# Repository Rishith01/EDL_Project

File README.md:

<!-- Do Not Change the below line. It will affect your workflow badge -->

<!-- ADD YOUR CHANGES AFTER THIS LINE -->

# SACE(Secure Adaptive Continuum Explorer)
**Team TUE-16 | Indian Institute of Technology Bombay**

---

## Team Members
* **Arijit Paul** (23B1219)
* **Arshit Singh** (23B1275)
* **Prithvi Sangam** (23B1292)
* **Rishith Gupta** (23B1234)
* **Veeresh S K** (23B1309)

---

## Project Abstract
This project investigates the practical implementation of **soft robotics** through the development of a modular, tentacle-based end effector on a continuum backbone. The system is engineered to navigate highly constrained environments and perform adaptive grasping of irregular objects. 

The architecture consists of a **continuum robotic arm featuring four flexible segments** capable of extending from a compact enclosure. By integrating 10 degrees of freedom (DOF), tendon-driven actuation, and real-time visual feedback, the robot demonstrates the capability of compliant structures to achieve dexterity and safety in applications where traditional rigid-link manipulators are insufficient.

---

## Key Technical Features
* **Deployable Mechanism:** Engineered for high spatial efficiency, allowing the arm to extend from a compact housing for maximum reach-to-storage ratio.
* **Continuum Kinematics:** A multi-link flexible structure that facilitates smooth, non-discrete bending for complex maneuvering in tight spaces.
* **Adaptive Morphology:** The tentacle-inspired design conforms naturally to the geometry of target objects, ensuring secure grasping through compliant contact.
* **Teleoperated Control:** Real-time operation via a gaming controller/click based interface, mapping user input directly to multi-segment motion.
* **Integrated Vision System:** An endoscope camera provides a live stream to the operator for precise navigation and targeting.
* **Active Safety Array:** Integrated limit switches detect external obstacles and mechanical limits to prevent system damage and ensure safe motion.
* **Modularity:** The system is partitioned into independent subsystems, allowing for streamlined repair, scaling, and iterative refinement.

---

## System Overview

### Hardware Architecture
* **Controller Architecture:** Dual Raspberry Pi Pico microcontrollers configured in a Master–Slave hierarchy to distribute real-time processing loads.
* **Motor Control:** Three Adafruit FeatherWing Motor Drivers, selected for their high-density power management and compact footprint.
* **Actuation:** 11 N20 micro-gear motors dedicated to tendon-driven link manipulation through specialized differential spools.
* **Sensing Array:** 16 Limit Switches (distributed as 4 per continuum segment) for obstacle detection and motion constraint.
* **Vision:** A high-resolution endoscope camera module for front-facing orientation and feedback with 60 degree field of view.
* **Electronics:** A custom-designed PCB for efficient power distribution and signal routing, including 12V to 3.3V power conversion.

### Software Architecture
* **Workstation Logic:** Python-based control scripts on the laptop for signal processing, controller mapping, and user interface management.
* **Embedded Firmware:** MicroPython-based scripts running on the Raspberry Pi Pico for low-level hardware control and motor actuation.
* **Visual Pipeline:** Python-based live feed processing for real-time operator guidance.
The flowcharts and execution logic are present in the folder READMEs. Refer to particular folder for more details.
---

## Working Principle
1.  **Input Acquisition:** The operator provides motion commands through a gaming controller/click and keyboard interface.
2.  **Signal Processing:** The laptop-based Python environment translates given commands into specific link-actuation commands and calculates which link is to move how much using our control algorithm.
3.  **Command Dispatch:** Control signals are transmitted to the Master Raspberry Pi Pico.
4.  **Distributed Execution:** The Master Pico coordinates with the Slave Pico and the motor driver array to execute precise motor rotations.
5.  **Actuation:** N20 motors rotate the differential spools, pulling tendons to induce controlled bending in the continuum segments.
6.  **Feedback Loop:** Real-time visual data from the camera and tactile data from the limit switches are monitored to guide navigation and prevent collisions.

---

## Final Deliverables

The project delivers a fully functional soft robotic system with the following capabilities:

- **Continuum Robotic Arm System**
  - A four-segment tendon-driven continuum arm capable of smooth, multi-directional bending  
  - Designed to navigate constrained environments with high flexibility  

- **Tentacle-Based End Effector**
  - A compliant gripper capable of adaptive grasping of irregular objects  
  - Independently actuated for controlled gripping  

- **Teleoperation Interface**
  - Real-time control using keyboard, mouse, and gaming controller  
  - Supports intuitive interaction through a camera-based interface  

- **Vision-Guided Operation**
  - Integrated endoscope camera providing live visual feedback  
  - Enables precise navigation and targeting  

- **Safety Mechanism**
  - Limit switch array for obstacle detection and motion constraint  
  - Automatic escape responses to prevent system damage  

- **Custom Embedded Control System**
  - Dual Raspberry Pi Pico architecture (Master–Slave)  
  - Distributed control for motor actuation and hardware interfacing  

- **Mechanical and Electronic Integration**
  - Fully assembled system including:
    - Custom PCB  
    - Motor driver integration  
    - Tendon-driven actuation system  

- **User Interface and Control Software**
  - Python-based host system for trajectory planning and control  
  - MicroPython firmware for real-time embedded execution  

---

## Repository Structure

```plaintext
├── src/                # Source code (MicroPython + Python)
├── pcb/                # PCB designs and schematics
│   └── PCB1/
│       ├── design.brd
│       ├── schematic.src
│       └── pictures/   # Fabricated PCB and Fusion 360 layouts
├── 3d_models/          # CAD models (Fusion 360)
│   ├── tentacle/
│   ├── continuum/
│   ├── base_plate/
|   ├── enclosure/
│   ├── spool/
|   └── motor_mount/
├── reports/            # Project Milestone Documentation
│   ├── milestone0/
│   ├── milestone1/
│   ├── milestone2/
|   ├── milestone3/
│   └── milestone4/
├── others/
│   ├── user_manual/    # Operational instructions
│   ├── presentation/   # System demonstration
|       ├── slides/
│       └── video/    
|   ├── images/         # Images of final setup
|   ├── extras/         # Extra images and videos
|   └── diagrams/       # Relevant diagrams
├── bom.xls             # Detailed Bill of Materials
└── README.md
```

## Repository Walkthrough

### src/
Contains all source code for the system, including:
- MicroPython code for the Raspberry Pi Pico, master and slave RPi (motor control, hardware interfacing)
- Python-based host code for user interaction, trajectory planning, and communication  

Each subfolder is organized based on the execution platform and includes relevant README files describing usage and setup.

---

### pcb/
Includes all PCB-related design files and documentation:
- Schematic and layout files for the custom PCB  
- Fabrication outputs and board design files  
- Images of the fabricated PCB and assembled boards  

The PCB integrates motor drivers, power distribution, and control interfaces required for system operation.

---

### 3d_models/
Contains all mechanical CAD designs used in the project.  
The models are organized into subsystem-level folders:
- **tentacle and top_link/** – End-effector for gripping and top link continuum link
- **continuum/** – Flexible links enabling motion  
- **base_plate/** – Structural base and motor mounting  
- **enclosure/** – Outer housing (laser-cut design)  
- **spools/** – Tendon winding mechanisms  
- **Motor Mount/** – Motor holding structures  

Each folder includes design files, images, and descriptions of functionality and assembly.

---

### reports/
Contains all milestone reports documenting the project lifecycle:
- Concept development  
- Design iterations  
- Implementation progress  
- Final system evaluation  

All reports are provided in PDF format.

---

### others/
Contains supporting materials required for understanding and operating the system:
- **user_manual/** – Step-by-step instructions for setup and operation  
- **presentation/** – Slides and demonstration video  
- **images/** – Photographs of the final assembled system  
- **diagrams/** – Wiring diagrams and system-level representations
- **extras/** - Extra images and videos during testing and prototyping

---

### bom.xls
A detailed Bill of Materials listing all components used in the project, including:
- Electronic components  
- Mechanical parts  
- Consumables and fabrication materials  

Each entry includes quantity, description, and source information.

---

### README.md
The root documentation file providing:
- Project overview and objectives  
- System description  
- Repository structure  
- Key features and functionality  
---

## Technical Constraints and Operational Limits
The current design represents a balance between mechanical performance and the physical limitations of the materials and space.

1. **Bending Threshold**: Empirical testing established a stable operational limit of approximately 30° per link. Beyond this angle, mechanical stress increases significantly, contributing to tendon slack issues within the actuation system.

2. **Control Paradigm**: Currently restricted to manual teleoperation; autonomous path planning and inverse kinematics are not yet implemented.

3. **Backbone Hysteresis and Droop**: The use of glue gun sticks as a central backbone introduces stability issues. After bending, the backbone may fail to return to a perfectly linear state, causing the robot to droop. Ensuring the backbone is fixed at the start and end of each link segment is critical for maintaining a consistent neutral axis.

4. **Tendon Dynamics**: Issues regarding tendon slack and potential thread interference in the shared spool design persist during extreme ranges of motion.

---

## Course Reflection and Learnings

### Technical Learnings

This project provided hands-on experience across multiple domains:

- **Mechanical Design**
  - Designing for tolerances and iterative prototyping  
  - Understanding trade-offs between flexibility and structural strength  
  - Challenges in tendon-driven systems such as slack and routing  

- **Embedded Systems**
  - Working with dual microcontroller architecture (Master–Slave)  
  - Interfacing peripherals such as motor drivers, encoders, and port expanders  
  - Handling real-time constraints in MicroPython  

- **Control Systems**
  - Implementing coordinated multi-link motion  
  - Understanding limitations of open-loop control  
  - Practical challenges in achieving smooth motion  

- **PCB Design**
  - Designing and debugging custom PCBs  
  - Managing power distribution and signal routing  
  - Handling hardware failures and component sensitivity  

- **System Integration**
  - Combining mechanical, electrical, and software subsystems  
  - Debugging issues arising only during full system integration  

---

### Team Challenges and Adaptation

- **Subsystem Isolation and Testing**
  - Each subsystem (mechanical, electronics, software) was tested independently before integration  
  - This helped in identifying issues early and reducing debugging complexity  

- **Iterative Prototyping**
  - Multiple iterations were required, especially for:
    - Spool design  
    - Tentacle structure  
    - Continuum links  
  - Rapid prototyping enabled quick validation and refinement  

- **Cross-Domain Collaboration**
  - Team members developed working knowledge of other subsystems  
  - Ensured continuity when specific members were unavailable  

- **Integration Challenges**
  - Most issues arose during integration rather than individual subsystem development  
  - Required coordinated debugging sessions and time alignment among team members  

---

### Honest Reflection

- While the final system achieves the intended functionality, a significant portion of the effort was spent resolving **practical engineering challenges** rather than implementing advanced features  

- Mechanical reliability (tolerances, tendon routing, slack management) proved to be more critical and time-consuming than initially anticipated  

- Hardware failures (motor drivers, microcontrollers) highlighted the importance of robust electrical design and protection  

- The control system works effectively for manual operation, but lacks higher-level intelligence and automation  

- Overall, the project demonstrates a **working proof-of-concept**, but not a fully optimized or production-ready system  

---

### Incomplete Features and Limitations

The following aspects remain incomplete:

- **Autonomous Control**
  - No implementation of inverse kinematics or automated path planning  
  - Reason: Complexity of modeling continuum kinematics and time constraints  

- **Closed-Loop Feedback**
  - Limited use of encoder data for precise control  
  - Reason: Integration complexity and prioritization of basic functionality  

- **Robust Tendon Management**
  - Issues with slack, overlap, and spool behavior at extreme motions  
  - Reason: Mechanical design constraints and limited iteration time  

- **System Stability**
  - Vibrations and minor inaccuracies in motion  
  - Reason: Structural limitations and compact design constraints  

---

### Future Work 

- **Inverse Kinematics for Continuum Arms**
  - Develop simplified models for controlled positioning  

- **Improved Tendon Mechanism**
  - Dedicated spool designs with better separation and tension control  

- **Enhanced Feedback Control**
  - Utilize encoder data for closed-loop control  
  - Implement PID-based corrections  

- **Structural Improvements**
  - Replace glue stick backbone with engineered compliant structures  

- **Miniaturization**
  - Redesign base plate and enclosure for reduced footprint  

- **System Robustness**
  - Add electrical protection (snubbers, proper grounding, shielding)  

---

## Acknowledgements
We extend our sincere gratitude to Prof. Siddharth Tallur, Prof. Himanshu Bahirat, and Prof. P. C. Pandey for their continuous guidance and valuable insights throughout this project. We also acknowledge the support of Ankur, Maheshwar, the WEL RAs and TAs for their technical assistance during the development and debugging phases.

## Inspiration 
The inspiration for the tentacle end effector came from this youtube video of the spirobs bot: https://m.youtube.com/watch?v=Q2yYclPaEV0

Inspiration for the continuum arm came from this video from continnum robotics lab of university of toronto. https://m.youtube.com/watch?v=MxBeUQay8YM

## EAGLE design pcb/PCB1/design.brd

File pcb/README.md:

# PCB information and Post-Fabrication Modifications

This PCB was designed using **Autodesk Fusion 360 (Fusion Electronics)**. It consists of 2 RPIs(both communicate over I2C, one is connected to the laptop[master] and the other is the slave). Slave RPI collects encoder information and relays it to the main RPI. We did this because we were worried about the computing capability of a single RPI. The master RPI also controls 2 GPIO port expanders[MCP23S17](over SPI), which provide a means to get feedback using the limit switches. This RPI also controls the Adafruit Featherwing motor drivers(via I2C), 3 of the drivers are stacked on top of each other using stackable header pins. It also contains an AMS1117 3.3V LDO to power the logic using a 12V input. More information about the schematic is available in the image below.

Following fabrication, a few manual trace modifications (often referred to as "micro-surgeries" or bodge wires) are required on the physical board to correct an inconsistency with the SPI bus routing.

## Layout issue
### SPI issue
In the initial PCB design, the pin assignments for the **MCP23S17** (specifically the one closest to the Raspberry Pi) were mistakenly split across two different SPI buses. The original, incorrect routing was as follows:

* **`GP6`** (Pin 9, SPI0 SCK) -> MCP23S17 SPI SCK
* **`GP7`** (Pin 10, SPI0 TX) -> MCP23S17 SPI TX
* **`GP8`** (Pin 11, SPI1 RX) -> MCP23S17 SPI RX
* **`GP9`** (Pin 12, SPI0 CS) -> MCP23S17 SPI CS

### RPI VBUS issue
Main RPI's VSYS pin(Pin 39) was connected to the 3.3V power rail on the PCB. The issue was that the main RPI had to be connected to the laptop via a USB cable while operating the robot which caused the VSYS pin to output 5V as it was connected to the power line of the USB. This forced the bus to go to 5V and fried our LDO(AMS 1117).

## Fixes 
### Microsurgery
To maintain SPI consistency and ensure the interface operates on a unified bus, the SPI TX and SCK lines for this MCP23S17 must be manually reassigned. The following corrections were made on the fabricated board:

* **MCP23S17 SPI TX** (Pin 8) -> Reroute to **`GP14`** (Pin 19)
* **MCP23S17 SPI SCK** (Pin 9) -> Reroute to **`GP15`** (Pin 20)
  
### Cutting pin headers 
Originally, the 3.3V bus going towards the main RPI was cut, but then we realised that it provided power to the slave RPI and encoders down the line, so we had to solder the cut trace and cut the pin headers for VSYS and VBUS of the main RPI using flush cutters so that 5V and 3.3V are not shorted.

Here is the pico pinout for easy reference.

## Purpose of PCB
- Wiring Mangement
- Keeping the electronics in one compartment
- Connecting all power sources needed to one main power port
- Fixing Wire ends for N20 motor connectors ( There were too many motors, needed a way to sort and compile all motor connections )

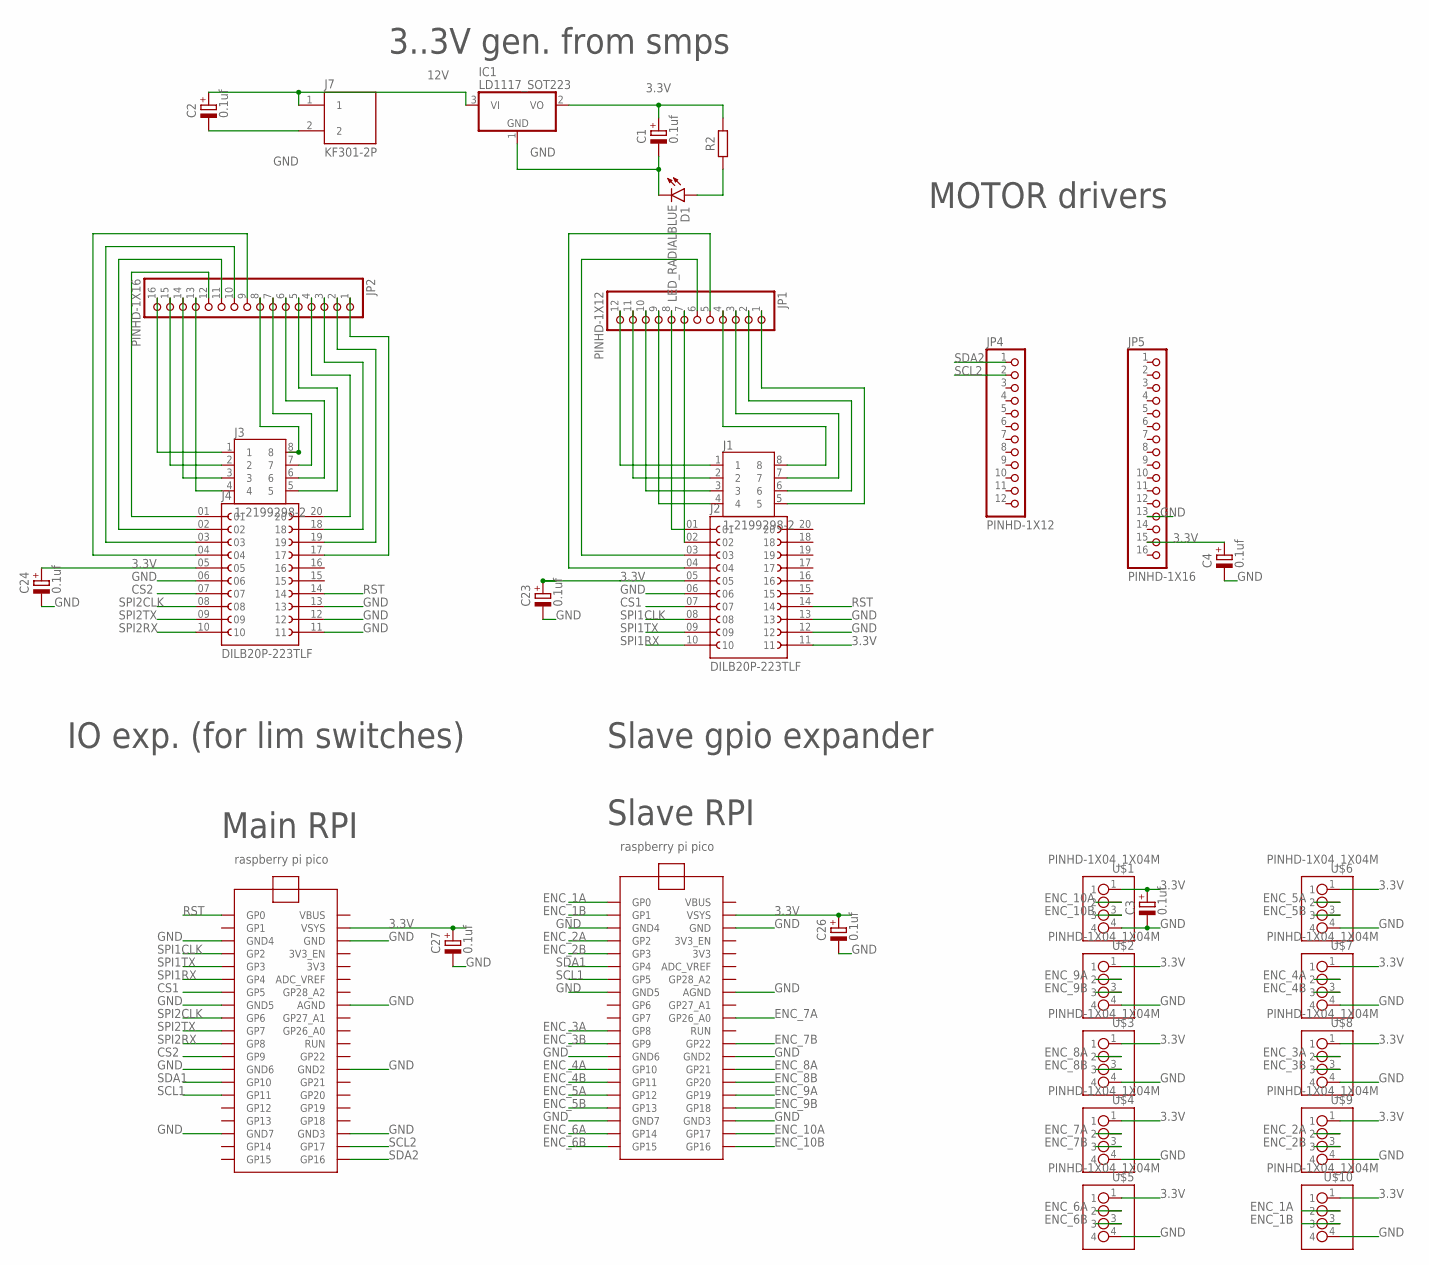
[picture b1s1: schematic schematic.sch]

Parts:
C1, C2, C3, C4, C23, C24, C26, C27: 0.1uf; CAPPRD254W65D500H1150B
D1: LED_RADIALBLUE; LEDRD254W60D565H860B_B
IC1: LD1117_SOT223; SOT230P700X170-4
J1, J3: 1-2199298-2; TE_1-2199298-2
J2, J4: DILB20P-223TLF; AMPHENOL_DILB20P-223TLF
J7: KF301-2P; HANDSON_KF301-2P
JP1, JP4: PINHD-1X12; 1X12
JP2, JP5: PINHD-1X16; 1X16
R2: R_AXIAL-11.7MM-PITCH; RESAD1176W63L850D250B
U2, U3: RASPBERRY_PI_PICO
U$1, U$2, U$3, U$4, U$5, U$6, U$7, U$8, U$9, U$10: PINHD-1X04_1X04M; 1X04

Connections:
3.3V: C1.1 (+), C3.1 (+), C4.1 (+), C23.1 (+), C24.1 (+), C26.1 (+), C27.1 (+), IC1.2 (VO), J2.05, J2.11, J4.05, JP5.15, R2.2, U2.VSYS, U3.VSYS, U$1.1, U$2.1, U$3.1, U$4.1, U$5.1, U$6.1, U$7.1, U$8.1, U$9.1, U$10.1
12V: C2.1 (+), IC1.3 (VI), J7.1
CS1: J2.07, U2.GP5
CS2: J4.07, U2.GP9
ENC_1A: U3.GP0, U$10.2
ENC_1B: U3.GP1, U$10.3
ENC_2A: U3.GP2, U$9.2
ENC_2B: U3.GP3, U$9.3
ENC_3A: U3.GP8, U$8.2
ENC_3B: U3.GP9, U$8.3
ENC_4A: U3.GP10, U$7.2
ENC_4B: U3.GP11, U$7.3
ENC_5A: U3.GP12, U$6.2
ENC_5B: U3.GP13, U$6.3
ENC_6A: U3.GP14, U$5.2
ENC_6B: U3.GP15, U$5.3
ENC_7A: U3.GP26_A0, U$4.2
ENC_7B: U3.GP22, U$4.3
ENC_8A: U3.GP21, U$3.2
ENC_8B: U3.GP20, U$3.3
ENC_9A: U3.GP19, U$2.2
ENC_9B: U3.GP18, U$2.3
ENC_10A: U3.GP17, U$1.2
ENC_10B: U3.GP16, U$1.3
GND: C1.2 (-), C2.2 (-), C3.2 (-), C4.2 (-), C23.2 (-), C24.2 (-), C26.2 (-), C27.2 (-), D1.C, IC1.1 (GND), J2.06, J2.12, J2.13, J4.06, J4.11, J4.12, J4.13, J7.2, JP5.13, U2.AGND, U2.GND, U2.GND2, U2.GND3, U2.GND4, U2.GND5, U2.GND6, U2.GND7, U3.AGND, U3.GND, U3.GND2, U3.GND3, U3.GND4, U3.GND5, U3.GND6, U3.GND7, U$1.4, U$2.4, U$3.4, U$4.4, U$5.4, U$6.4, U$7.4, U$8.4, U$9.4, U$10.4
GPA1: J3.8, JP2.8
LS1: J1.5, JP1.1
unnamed: D1.A, R2.1
unnamed: J1.1, JP1.12
unnamed: J1.2, JP1.11
unnamed: J1.3, JP1.10
unnamed: J1.4, JP1.9
unnamed: J2.01, JP1.8
unnamed: J1.8, JP1.4
unnamed: J1.7, JP1.3
unnamed: J2.02, JP1.7
unnamed: J2.03, JP1.6
unnamed: J2.04, JP1.5
unnamed: J3.1, JP2.16
unnamed: J3.2, JP2.15
unnamed: J3.3, JP2.14
unnamed: J3.4, JP2.13
unnamed: J4.01, JP2.12
unnamed: J1.6, JP1.2
unnamed: J4.02, JP2.11
unnamed: J4.03, JP2.10
unnamed: J4.04, JP2.9
unnamed: J3.7, JP2.7
unnamed: J3.6, JP2.6
unnamed: J3.5, JP2.5
unnamed: J4.20, JP2.4
unnamed: J4.18, JP2.3
unnamed: J4.19, JP2.2
unnamed: J4.17, JP2.1
RST: J2.14, J4.14, U2.GP0
SCL1: U2.GP11, U3.GP5
SCL2: JP4.2, U2.GP17
SDA1: U2.GP10, U3.GP4
SDA2: JP4.1, U2.GP16
SPI1CLK: J2.08, U2.GP2
SPI1RX: J2.10, U2.GP4
SPI1TX: J2.09, U2.GP3
SPI2CLK: J4.08, U2.GP6
SPI2RX: J4.10, U2.GP8
SPI2TX: J4.09, U2.GP7

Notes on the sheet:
Main RPI
Slave RPI
Slave gpio expander
IO exp. (for lim switches)
MOTOR drivers
3..3V gen. from smps

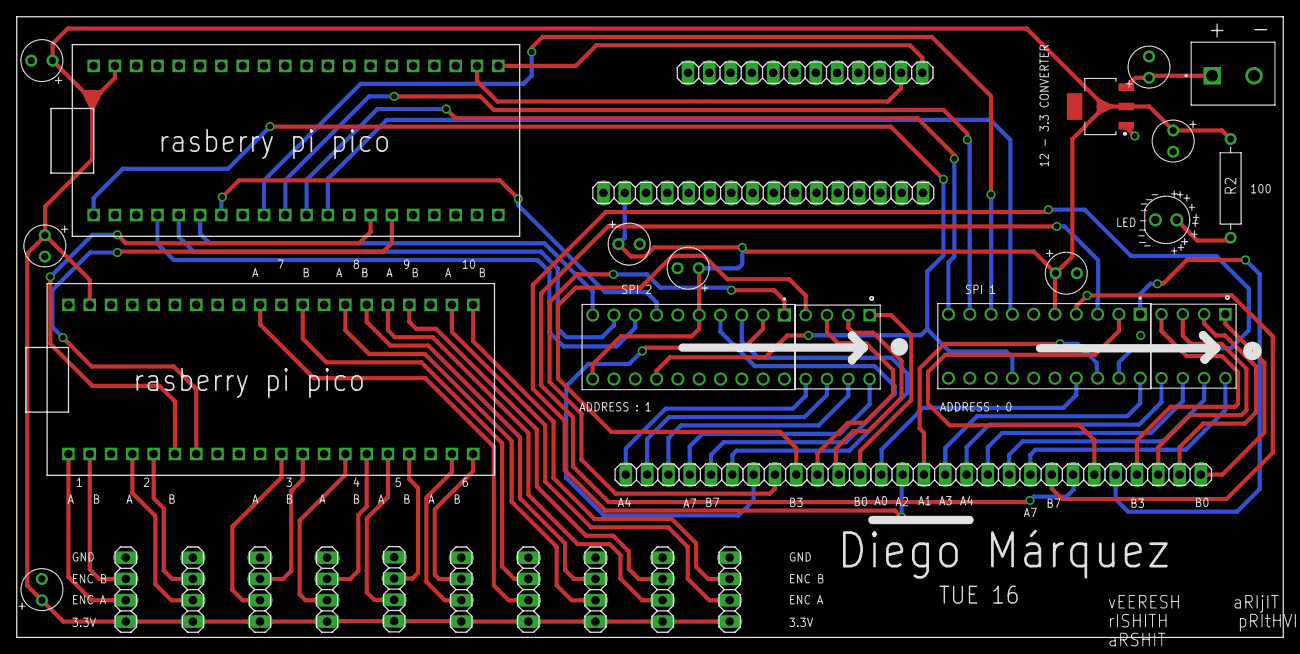
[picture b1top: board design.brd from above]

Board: 2 copper layers, 151.0 x 74.0 mm, 32 parts (0 on the bottom side), 65 nets.

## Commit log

2026-02-17 Test 1 and 2 as per Comprehensive README is done
2026-02-19 GUI interface done
2026-02-19 Working on RPI interfacing
2026-02-27 Updated Code for implemented limit switches and up,down movement
2026-03-03 Everything in UART now
2026-03-06 Limit switch incorporated
2026-03-10 Micropython implemented
2026-03-10 Add VS Code MicroPython setup guide for import resolution
2026-03-10 Improve config completeness and cross-file integration
2026-04-22 Updated Repo
